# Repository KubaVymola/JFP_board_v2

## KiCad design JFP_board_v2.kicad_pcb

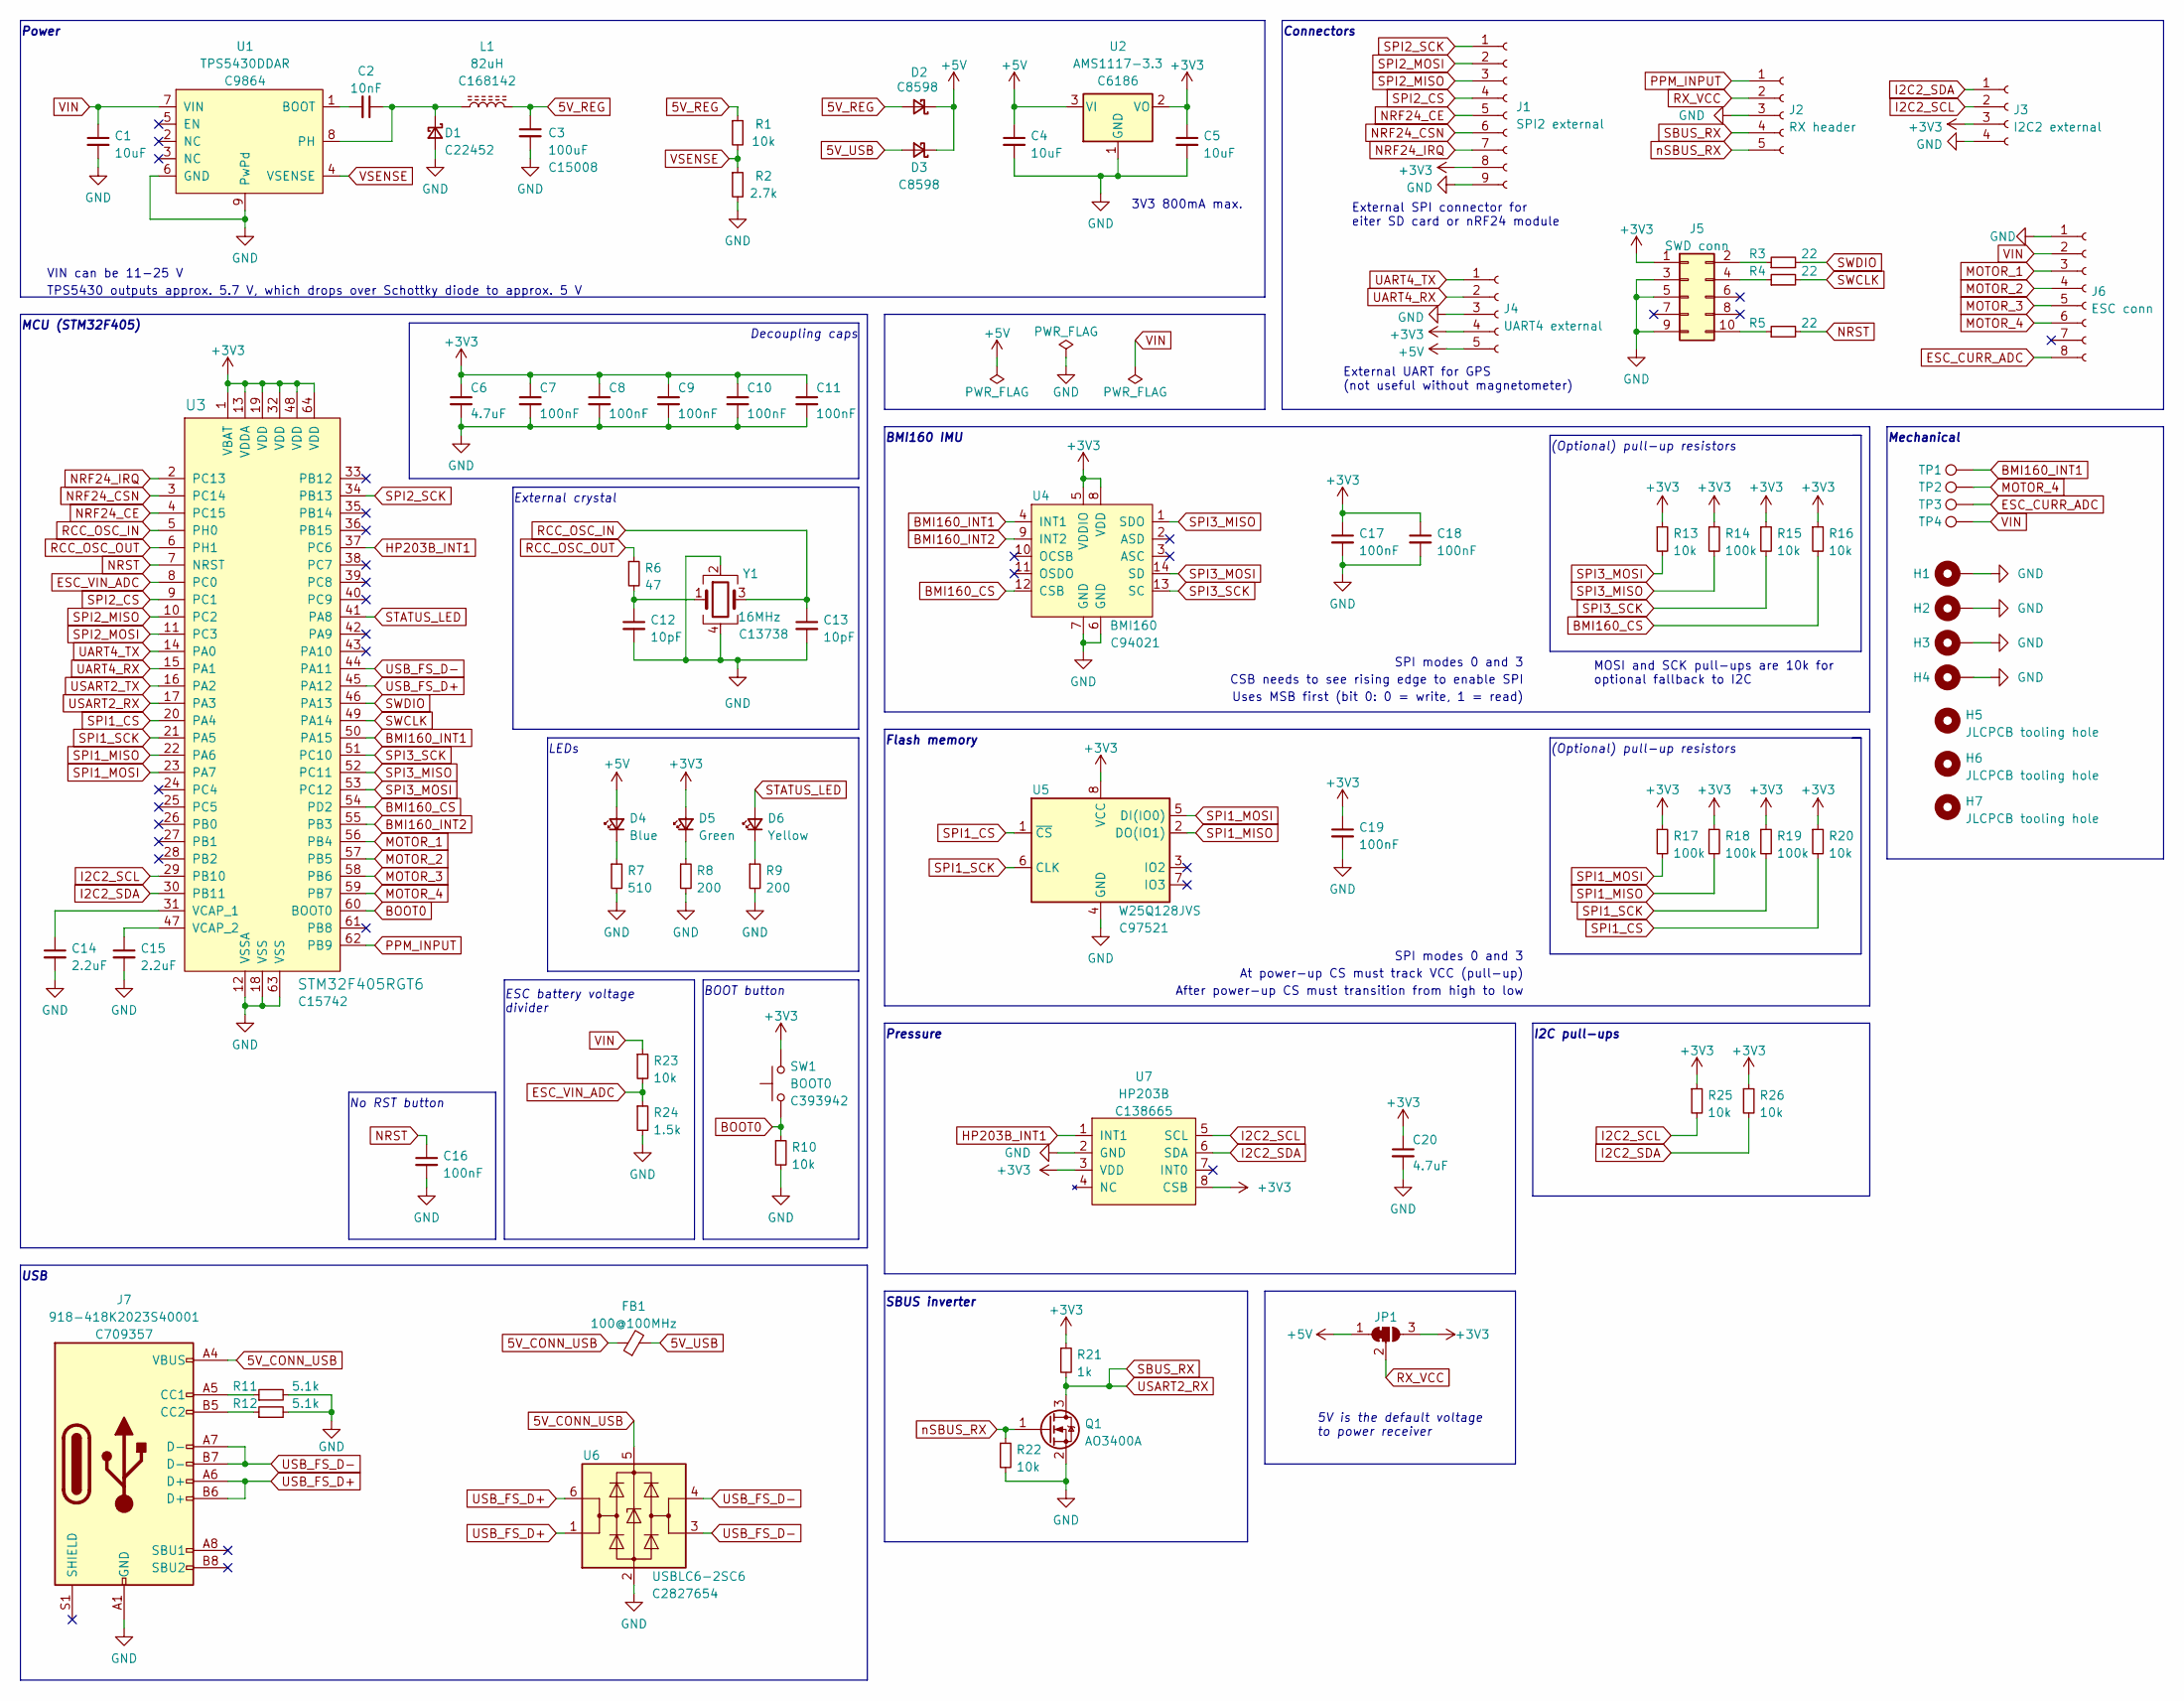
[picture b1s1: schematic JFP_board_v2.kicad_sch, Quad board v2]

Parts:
C1: 10uF; C_0805_2012Metric; LCSC C440198
C2: 10nF; C_0603_1608Metric; LCSC C57112
C3: 100uF; C_1206_3216Metric; LCSC C15008
C4, C5: 10uF; C_0603_1608Metric; LCSC C19702
C6, C20: 4.7uF; C_0603_1608Metric; LCSC C19666
C7, C8, C9, C10, C11, C16, C17, C18, C19: 100nF; C_0402_1005Metric; LCSC C307331
C12, C13: 10pF; C_0402_1005Metric; LCSC C32949
C14, C15: 2.2uF; C_0402_1005Metric; LCSC C12530
D1: D_Schottky_Small; D_SMA; LCSC C22452
D2, D3: D_Schottky_Small; D_SOD-123; LCSC C8598
D4: Blue; LED_0603_1608Metric; LCSC C72041
D5: Green; LED_0603_1608Metric; LCSC C72043
D6: Yellow; LED_0603_1608Metric; LCSC C72038
FB1: 100@100MHz; L_0805_2012Metric; LCSC C1015
H1, H2, H3, H4: MountingHole_Pad; Mounting_hole_GND_M3_4.5mm
H5, H6, H7: JLCPCB tooling hole; JLCPCB_tooling_hole_1.152mm
J1: SPI2 external; Pads_1.8mm_01x09
J2: RX header; Pads_1.8mm_01x05
J3: I2C2 external; Pads_1.8mm_01x04
J4: UART4 external; Pads_1.8mm_01x05
J5: SWD conn; PinHeader_2x05_P1.27mm_Vertical
J6: ESC conn; JST_SH_SM08B-SRSS-TB_1x08-1MP_P1.00mm_Horizontal
J7: 918-418K2023S40001; USB_C_Receptacle_HRO_TYPE-C-31-M-12; LCSC C709357
JP1: SolderJumper_3_Bridged12; SolderJumper-3_P1.3mm_Bridged12_RoundedPad1.0x1.5mm
L1: 82uH; SMD-8x8x4; LCSC C168142
Q1: AO3400A; SOT-23; LCSC C20917
R1: 10k; R_0603_1608Metric; LCSC C25804
R2: 2.7k; R_0603_1608Metric; LCSC C13167
R3, R4, R5: 22; R_0402_1005Metric; LCSC C25092
R6: 47; R_0402_1005Metric; LCSC C25118
R7: 510; R_0402_1005Metric; LCSC C25123
R8, R9: 200; R_0402_1005Metric; LCSC C25087
R10, R13, R15, R16, R20, R22, R23, R25, R26: 10k; R_0402_1005Metric; LCSC C25744
R11, R12: 5.1k; R_0402_1005Metric; LCSC C25905
R14, R17, R18, R19: 100k; R_0402_1005Metric; LCSC C25741
R21: 1k; R_0402_1005Metric; LCSC C11702
R24: 1.5k; R_0402_1005Metric; LCSC C25867
SW1: BOOT0; TS24CA; LCSC C393942
TP1, TP2, TP3, TP4: TestPoint; TestPoint_Pad_D1.0mm
U1: TPS5430DDAR; HSOP-8-1EP_3.9x4.9mm_P1.27mm_EP2.41x3.1mm; jlcpcb C9864
U2: AMS1117-3.3; SOT-223-3_TabPin2; LCSC C6186
U3: STM32F405RGT6; LQFP-64_10x10mm; MPN STM32F405RGT6; Digi-Key_PN 497-11767-ND
U4: BMI160; MPN BMI160; Digi-Key_PN 828-1057-1-ND
U5: W25Q128JVS; SOIC-8_5.23x5.23mm_P1.27mm; LCSC C97521
U6: USBLC6-2SC6; SOT-23-6; LCSC C2827654
U7: HP203B; LGA-8_3.6x3.8x0.9P; LCSC C138665
Y1: 16MHz; Crystal_SMD_3225-4Pin_3.2x2.5mm; LCSC C13738

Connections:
5V_CONN_USB: FB1.1, J7.A4 (VBUS), J7.A9 (VBUS), J7.B4 (VBUS), J7.B9 (VBUS), U6.5 (VBUS)
5V_REG: C3.1, D2.2 (A), L1.2, R1.1
5V_USB: D3.2 (A), FB1.2
+3V3: C5.1, C6.1, C7.1, C8.1, C9.1, C10.1, C11.1, C17.1, C18.1, C19.1, C20.1, D5.2 (A), J1.8, J3.3, J4.4, J5.1, JP1.3 (B), R13.1, R14.1, R15.1, R16.1, R17.1, R18.1, R19.1, R20.1, R21.1, R25.1, R26.1, SW1.2, U2.2 (VO), U3.1 (VBAT), U3.13 (VDDA), U3.19 (VDD), U3.32 (VDD), U3.48 (VDD), U3.64 (VDD), U4.5 (VDDIO), U4.8 (VDD), U5.8 (VCC), U7.3 (VDD), U7.8 (CSB)
+5V: C4.1, D2.1 (K), D3.1 (K), D4.2 (A), J4.5, JP1.1 (A), U2.3 (VI)
BMI160_CS: R16.2, U3.54 (PD2), U4.12 (CSB)
BMI160_INT1: TP1.1, U3.50 (PA15), U4.4 (INT1)
BMI160_INT2: U3.55 (PB3), U4.9 (INT2)
BOOT0: R10.1, SW1.1, U3.60 (BOOT0)
ESC_CURR_ADC: J6.8, TP3.1
ESC_VIN_ADC: R23.2, R24.1, U3.8 (PC0)
GND: C1.2, C3.2, C4.2, C5.2, C6.2, C7.2, C8.2, C9.2, C10.2, C11.2, C12.2, C13.2, C14.2, C15.2, C16.2, C17.2, C18.2, C19.2, C20.2, D1.2 (A), H1.1, H2.1, H3.1, H4.1, J1.9, J2.3, J3.4, J4.3, J5.3, J5.5, J5.9, J6.1, J7.A1 (GND), J7.A12 (GND), J7.B1 (GND), J7.B12 (GND), Q1.2 (S), R2.2, R7.2, R8.2, R9.2, R10.2, R11.2, R12.2, R22.2, R24.2, U1.6 (GND), U1.9 (PwPd), U2.1 (GND), U3.12 (VSSA), U3.18 (VSS), U3.63 (VSS), U4.6 (GND), U4.7 (GND), U5.4 (GND), U6.2 (GND), U7.2 (GND), Y1.2, Y1.4
HP203B_INT1: U3.37 (PC6), U7.1 (INT1)
I2C2_SCL: J3.2, R25.2, U3.29 (PB10), U7.5 (SCL)
I2C2_SDA: J3.1, R26.2, U3.30 (PB11), U7.6 (SDA)
MOTOR_1: J6.3, U3.56 (PB4)
MOTOR_2: J6.4, U3.57 (PB5)
MOTOR_3: J6.5, U3.58 (PB6)
MOTOR_4: J6.6, TP2.1, U3.59 (PB7)
NRF24_CE: J1.5, U3.4 (PC15)
NRF24_CSN: J1.6, U3.3 (PC14)
NRF24_IRQ: J1.7, U3.2 (PC13)
NRST: C16.1, R5.2, U3.7 (NRST)
unnamed: C2.1, D1.1 (K), L1.1, U1.8 (PH)
unnamed: C2.2, U1.1 (BOOT)
unnamed: C12.1, R6.2, Y1.1
unnamed: C14.1, U3.31 (VCAP_1)
unnamed: C15.1, U3.47 (VCAP_2)
unnamed: D4.1 (K), R7.1
unnamed: D5.1 (K), R8.1
unnamed: D6.1 (K), R9.1
unnamed: J5.2, R3.1
unnamed: J5.4, R4.1
unnamed: J5.10, R5.1
unnamed: J7.A5 (CC1), R11.1
unnamed: J7.B5 (CC2), R12.1
PPM_INPUT: J2.1, U3.62 (PB9)
RCC_OSC_IN: C13.1, U3.5 (PH0), Y1.3
RCC_OSC_OUT: R6.1, U3.6 (PH1)
RX_VCC: J2.2, JP1.2 (C)
SBUS_RX: J2.4, Q1.3 (D), R21.2, U3.17 (PA3)
SPI1_CS: R20.2, U3.20 (PA4), U5.1 (~CS)
SPI1_MISO: R18.2, U3.22 (PA6), U5.2 (DO(IO1))
SPI1_MOSI: R17.2, U3.23 (PA7), U5.5 (DI(IO0))
SPI1_SCK: R19.2, U3.21 (PA5), U5.6 (CLK)
SPI2_CS: J1.4, U3.9 (PC1)
SPI2_MISO: J1.3, U3.10 (PC2)
SPI2_MOSI: J1.2, U3.11 (PC3)
SPI2_SCK: J1.1, U3.34 (PB13)
SPI3_MISO: R14.2, U3.52 (PC11), U4.1 (SDO)
SPI3_MOSI: R13.2, U3.53 (PC12), U4.14 (SD)
SPI3_SCK: R15.2, U3.51 (PC10), U4.13 (SC)
STATUS_LED: D6.2 (A), U3.41 (PA8)
SWCLK: R4.2, U3.49 (PA14)
SWDIO: R3.2, U3.46 (PA13)
UART4_RX: J4.2, U3.15 (PA1)
UART4_TX: J4.1, U3.14 (PA0)
USART2_TX: U3.16 (PA2)
USB_FS_D+: J7.A6 (D+), J7.B6 (D+), U3.45 (PA12), U6.1 (I/O1), U6.6 (I/O1)
USB_FS_D-: J7.A7 (D-), J7.B7 (D-), U3.44 (PA11), U6.3 (I/O2), U6.4 (I/O2)
VIN: C1.1, J6.2, R23.1, TP4.1, U1.7 (VIN)
VSENSE: R1.2, R2.1, U1.4 (VSENSE)
nSBUS_RX: J2.5, Q1.1 (G), R22.1

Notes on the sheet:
SPI modes 0 and 3
Decoupling caps
Flash memory
CSB needs to see rising edge to enable SPI
At power-up CS must track VCC (pull-up)
VIN can be 11-25 V
MCU (STM32F405)
USB
Uses MSB first (bit 0: 0 = write, 1 = read)
SBUS inverter
LEDs
3V3 800mA max.
External SPI connector for eiter SD card or nRF24 module
TPS5430 outputs approx. 5.7 V, which drops over Schottky diode to approx. 5 V
5V is the default voltage to power receiver
BMI160 IMU
(Optional) pull-up resistors
No RST button
ESC battery voltage divider
Pressure
Connectors
BOOT button
I2C pull-ups
After power-up CS must transition from high to low
External crystal
Power
Mechanical
External UART for GPS (not useful without magnetometer)
MOSI and SCK pull-ups are 10k for optional fallback to I2C

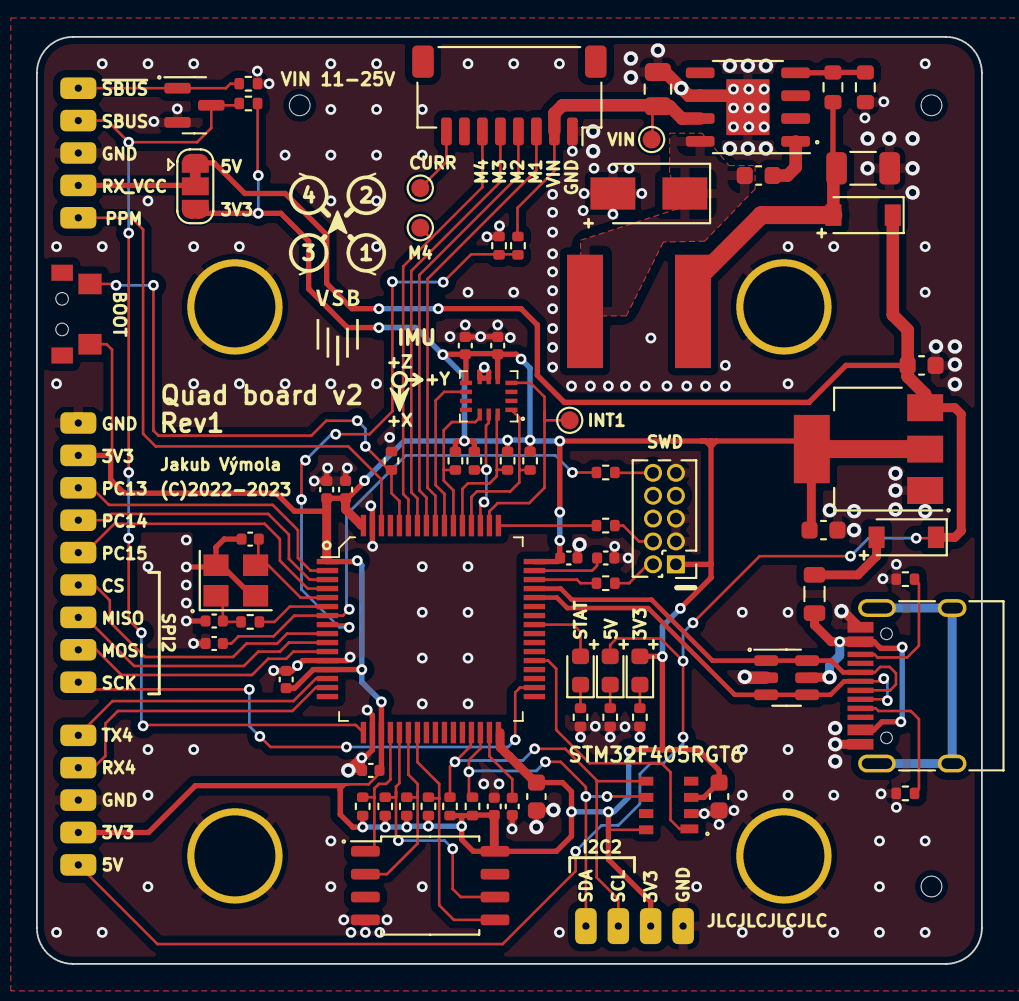
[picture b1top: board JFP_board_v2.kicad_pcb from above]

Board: 2 copper layers, 52.5 x 51.5 mm, 86 parts (0 on the bottom side), 62 nets.

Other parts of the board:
REFBMIAXES: BMI_160_axes
REFQUAD: Drone_props
REFVSBLOGO: d2f2efcc-2693-47d5-a2c4-dd12ed3edea1

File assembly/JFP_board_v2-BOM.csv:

Comment,Designator,Footprint,LCSC
"10uF","C1","Capacitor_SMD:C_0805_2012Metric","C440198"
"10pF","C12,C13","Capacitor_SMD:C_0402_1005Metric","C32949"
"2.2uF","C14,C15","Capacitor_SMD:C_0402_1005Metric","C12530"
"10nF","C2","Capacitor_SMD:C_0603_1608Metric","C57112"
"100uF","C3","Capacitor_SMD:C_1206_3216Metric","C15008"
"10uF","C4,C5","Capacitor_SMD:C_0603_1608Metric","C19702"
"4.7uF","C6,C20","Capacitor_SMD:C_0603_1608Metric","C19666"
"100nF","C7,C8,C9,C10,C11,C16,C17,C18,C19","Capacitor_SMD:C_0402_1005Metric","C307331"
"D_Schottky_Small","D1","Diode_SMD:D_SMA","C22452"
"D_Schottky_Small","D2,D3","Diode_SMD:D_SOD-123","C8598"
"Blue","D4","LED_SMD:LED_0603_1608Metric","C72041"
"Green","D5","LED_SMD:LED_0603_1608Metric","C72043"
"Yellow","D6","LED_SMD:LED_0603_1608Metric","C72038"
"100@100MHz","FB1","Inductor_SMD:L_0805_2012Metric","C1015"
"MountingHole_Pad","H1,H2,H3,H4","_custom_footprints:Mounting_hole_GND_M3_4.5mm",""
"JLCPCB tooling hole","H5,H6,H7","_custom_footprints:JLCPCB_tooling_hole_1.152mm",""
"SPI2 external","J1","_custom_footprints:Pads_1.8mm_01x09",""
"RX header","J2","_custom_footprints:Pads_1.8mm_01x05",""
"I2C2 external","J3","_custom_footprints:Pads_1.8mm_01x04",""
"UART4 external","J4","_custom_footprints:Pads_1.8mm_01x05",""
"SWD conn","J5","Connector_PinHeader_1.27mm:PinHeader_2x05_P1.27mm_Vertical",""
"ESC conn","J6","Connector_JST:JST_SH_SM08B-SRSS-TB_1x08-1MP_P1.00mm_Horizontal",""
"918-418K2023S40001","J7","Connector_USB:USB_C_Receptacle_HRO_TYPE-C-31-M-12","C709357"
"SolderJumper_3_Bridged12","JP1","Jumper:SolderJumper-3_P1.3mm_Bridged12_RoundedPad1.0x1.5mm",""
"82uH","L1","_custom_footprints:SMD-8x8x4","C168142"
"AO3400A","Q1","Package_TO_SOT_SMD:SOT-23","C20917"
"10k","R1","Resistor_SMD:R_0603_1608Metric","C25804"
"10k","R10,R13,R15,R16,R20,R22,R23,R25,R26","Resistor_SMD:R_0402_1005Metric","C25744"
"5.1k","R11,R12","Resistor_SMD:R_0402_1005Metric","C25905"
"100k","R14,R17,R18,R19","Resistor_SMD:R_0402_1005Metric","C25741"
"2.7k","R2","Resistor_SMD:R_0603_1608Metric","C13167"
"1k","R21","Resistor_SMD:R_0402_1005Metric","C11702"
"1.5k","R24","Resistor_SMD:R_0402_1005Metric","C25867"
"22","R3,R4,R5","Resistor_SMD:R_0402_1005Metric","C25092"
"47","R6","Resistor_SMD:R_0402_1005Metric","C25118"
"510","R7","Resistor_SMD:R_0402_1005Metric","C25123"
"200","R8,R9","Resistor_SMD:R_0402_1005Metric","C25087"
"BOOT0","SW1","_custom_footprints:TS24CA","C393942"
"TestPoint","TP1,TP2,TP3,TP4","TestPoint:TestPoint_Pad_D1.0mm",""
"TPS5430DDAR","U1","Package_SO:HSOP-8-1EP_3.9x4.9mm_P1.27mm_EP2.41x3.1mm","C9864"
"AMS1117-3.3","U2","Package_TO_SOT_SMD:SOT-223-3_TabPin2","C6186"
"STM32F405RGT6","U3","digikey-footprints:LQFP-64_10x10mm","C15742"
"BMI160","U4","digikey-footprints:BMI160","C94021"
"W25Q128JVS","U5","Package_SO:SOIC-8_5.23x5.23mm_P1.27mm","C97521"
"USBLC6-2SC6","U6","Package_TO_SOT_SMD:SOT-23-6","C2827654"
"HP203B","U7","_custom_footprints:LGA-8_3.6x3.8x0.9P","C138665"
"16MHz","Y1","Crystal:Crystal_SMD_3225-4Pin_3.2x2.5mm","C13738"

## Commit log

2023-01-05 Added HP203B pressure sensor
2023-02-23 Production files

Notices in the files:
JFP_board_v2.kicad_pcb:
(C)2022-2023
JFP_board_v2.kicad_sch:
Copyright (C) 2022-2023 Jakub Výmola
